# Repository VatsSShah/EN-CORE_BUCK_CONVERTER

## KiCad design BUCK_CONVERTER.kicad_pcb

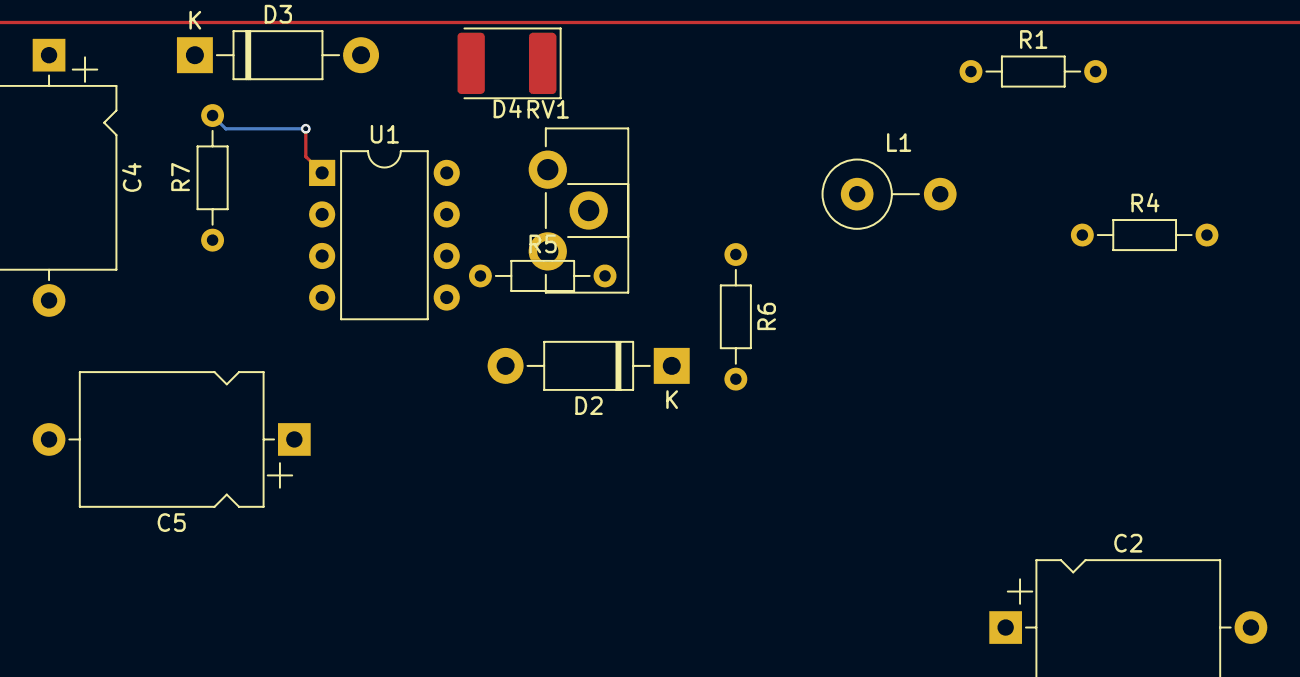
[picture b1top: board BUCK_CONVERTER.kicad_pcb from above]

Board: 2 copper layers, 14 parts (0 on the bottom side), 12 nets.

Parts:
C2: 47u; CP_Axial_L11.0mm_D8.0mm_P15.00mm_Horizontal
C4: 47n; CP_Axial_L11.0mm_D8.0mm_P15.00mm_Horizontal
C5: 10n; CP_Axial_L11.0mm_D8.0mm_P15.00mm_Horizontal
D2, D3: 1N4007; D_DO-41_SOD81_P10.16mm_Horizontal
D4: D_Schottky; D_2114_3652Metric
L1: 15u; L_Axial_L9.5mm_D4.0mm_P5.08mm_Vertical_Fastron_SMCC
R1: 8.5k; R_Axial_DIN0204_L3.6mm_D1.6mm_P7.62mm_Horizontal
R4, R5: 10k; R_Axial_DIN0204_L3.6mm_D1.6mm_P7.62mm_Horizontal
R6: 20k; R_Axial_DIN0204_L3.6mm_D1.6mm_P7.62mm_Horizontal
R7: 220; R_Axial_DIN0204_L3.6mm_D1.6mm_P7.62mm_Horizontal
RV1: 100k; Potentiometer_ACP_CA9-H2,5_Horizontal
U1: LM555xN; DIP-8_W7.62mm

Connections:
0: C2.2, C4.2, C5.2, D4.2 (A), R4.2, R7.2, U1.1 (GND)
+10V: R5.1, U1.8 (VCC)
unnamed: C2.1, L1.2, R1.1
unnamed: C4.1, D2.2 (A), D3.1 (K), U1.2 (TR), U1.6 (THR)
unnamed: D2.1 (K), R6.2
unnamed: D3.2 (A), RV1.2, U1.7 (DIS)
unnamed: D4.1 (K), L1.1
unnamed: R7.1, U1.3 (Q)
unnamed: R1.2, R4.1
unnamed: R5.2, RV1.1
unnamed: R6.1, RV1.3
unnamed: C5.1, U1.5 (CV)
